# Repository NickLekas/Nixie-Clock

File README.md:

v1 is broken and required some bodge wires to work. I have not updated the schematic and PCB to correct my mistakes. It also has some deficencies in the dimming circuit resulint in a quiet, but audible whine.

v2 is in progress and will fix many issues and make the clock easier to update. It wil be using an RP2040.

Features
- Automatic time seting using GPS
- User sets their time zone using dip switches
- Tubes dim with ambient light
- Day light savings time will be controlled using a +/-1 switch 
- Plenty of test points for testing and hacking
- USB C for power and data

The goal of this is to be a program once project so the end user will never need to plug it into a computer. But if they do, the RP2040 will make firmware updates easy

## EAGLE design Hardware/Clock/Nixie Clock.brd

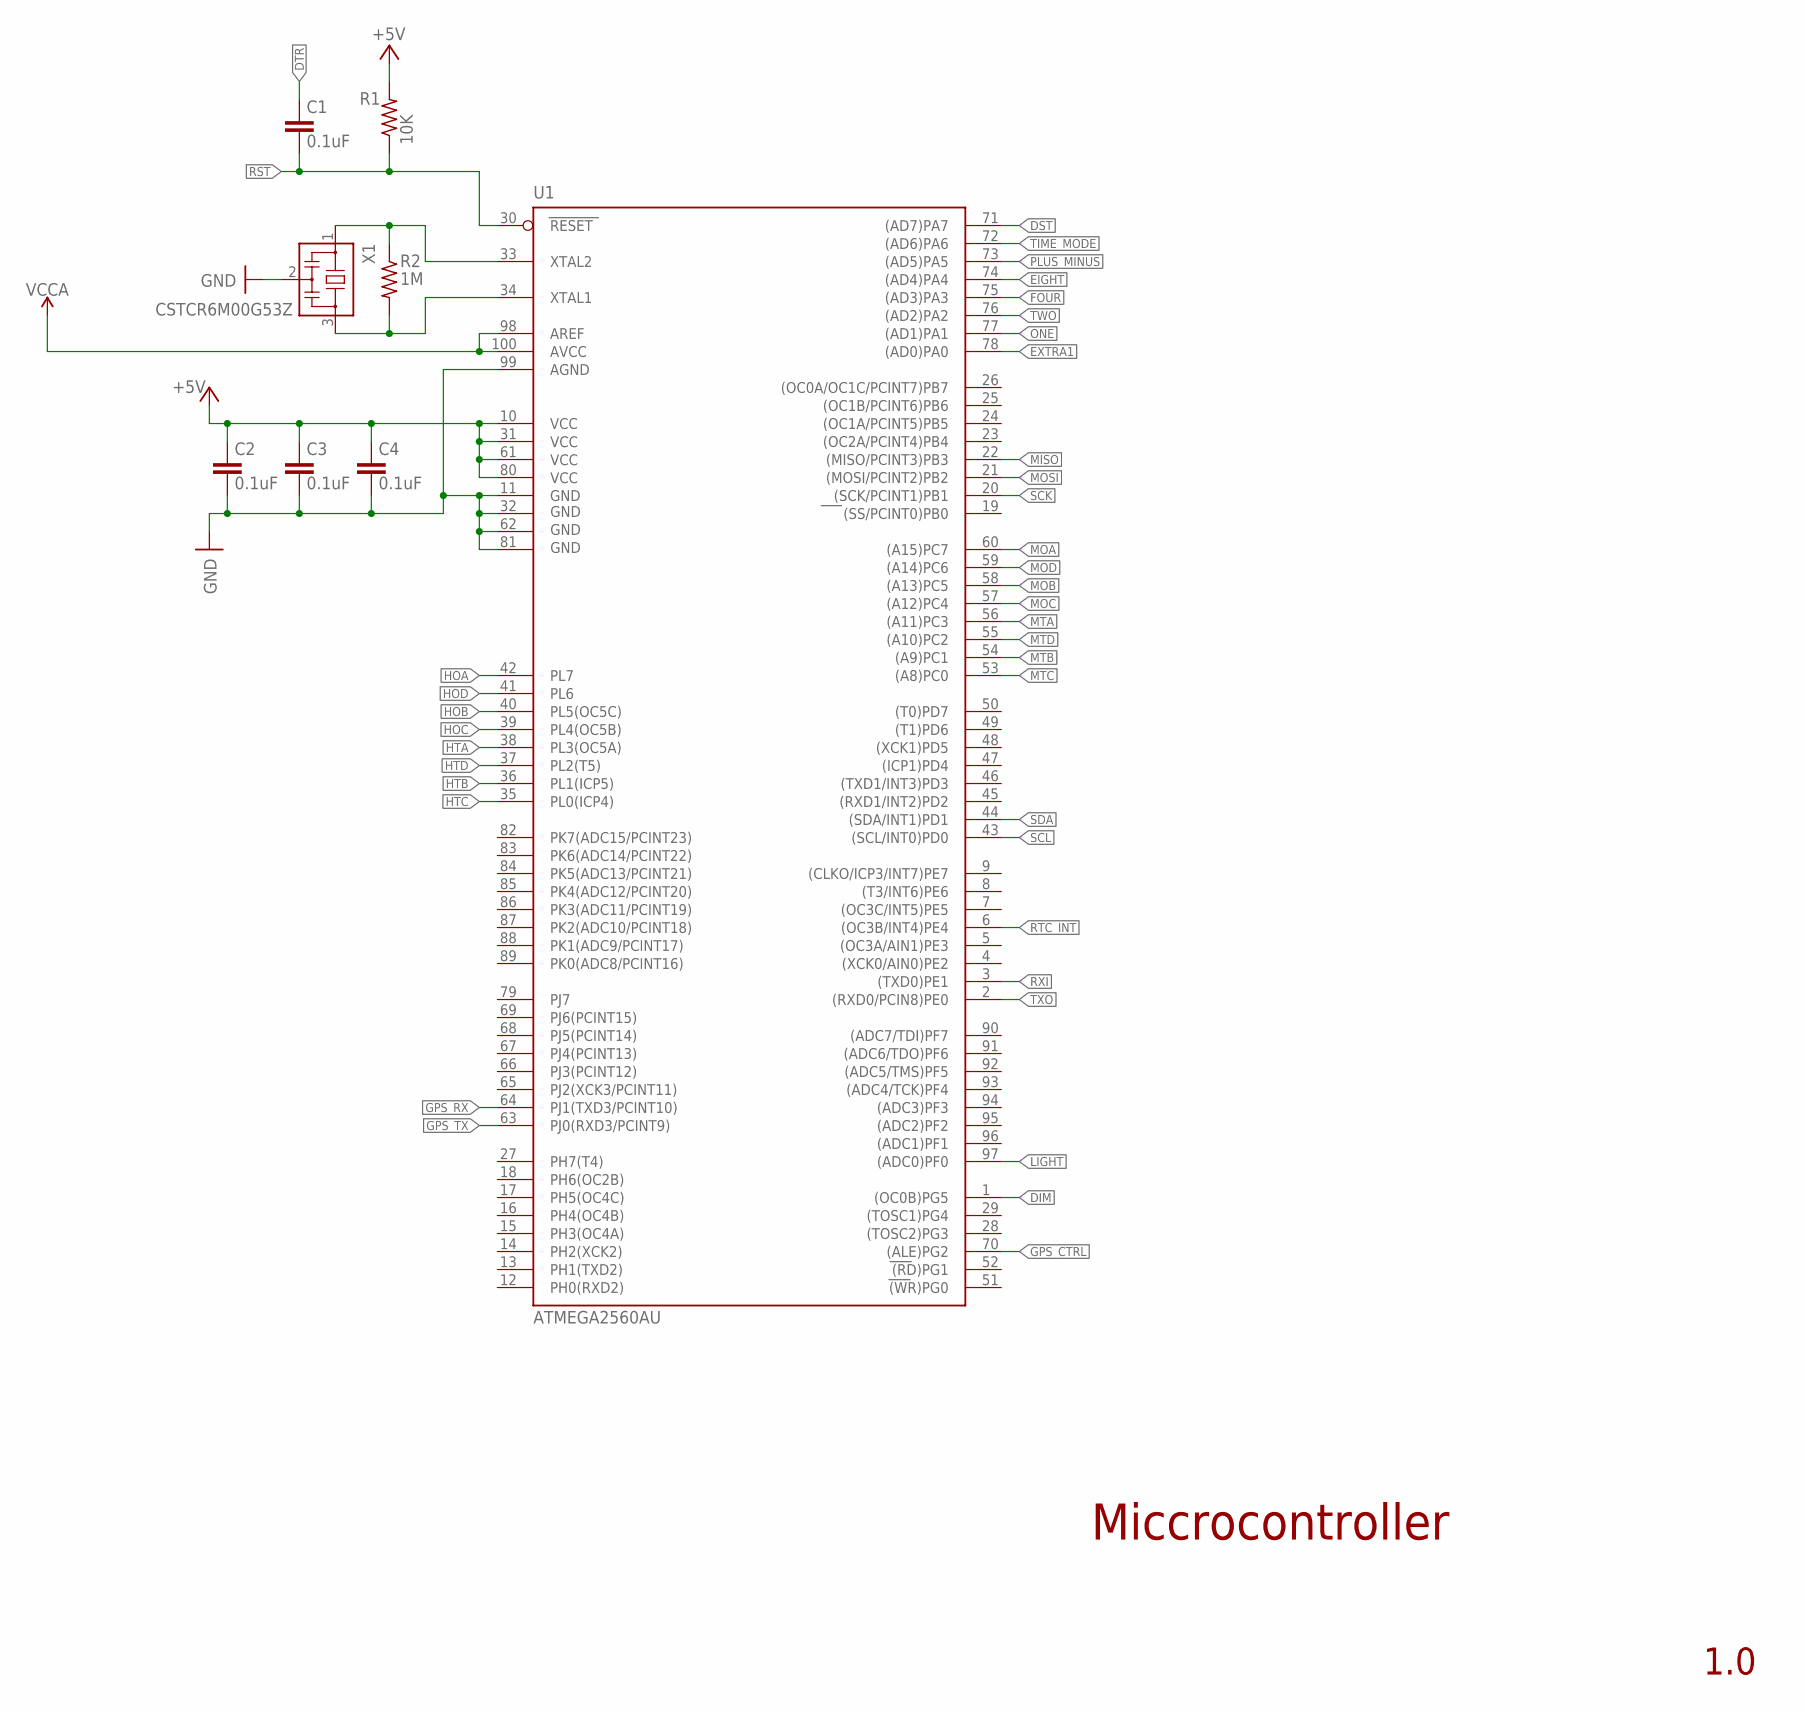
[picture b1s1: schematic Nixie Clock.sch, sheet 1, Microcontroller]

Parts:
C1, C2, C3, C4: 0.1uF; C0603
R1: 10K; R0603
R2: 1M; R0603
U1: ATMEGA2560AU; TQFP100; MPN ATMEGA2560-16AU
X1: CSTCR6M00G53Z; CSTCR6M; MPN CSTCE16M0V13C99-R0

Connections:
+5V: C2.1, C3.1, C4.1, R1.2, U1.10 (VCC), U1.31 (VCC1), U1.61 (VCC2), U1.80 (VCC3); also elsewhere on the board
DIM: U1.1 ((OC0B)PG5); also elsewhere on the board
DST: U1.71 ((AD7)PA7); also elsewhere on the board
DTR: C1.1; also elsewhere on the board
EIGHT: U1.74 ((AD4)PA4); also elsewhere on the board
EXTRA1: U1.78 ((AD0)PA0); also elsewhere on the board
FOUR: U1.75 ((AD3)PA3); also elsewhere on the board
GND: C2.2, C3.2, C4.2, U1.11 (GND), U1.32 (GND1), U1.62 (GND2), U1.81 (GND3), U1.99 (AGND), X1.2; also elsewhere on the board
GPS_CTRL: U1.70 ((ALE)PG2); also elsewhere on the board
GPS_RX: U1.64 (PJ1(TXD3/PCINT10)); also elsewhere on the board
GPS_TX: U1.63 (PJ0(RXD3/PCINT9)); also elsewhere on the board
HOA: U1.42 (PL7); also elsewhere on the board
HOB: U1.40 (PL5(OC5C)); also elsewhere on the board
HOC: U1.39 (PL4(OC5B)); also elsewhere on the board
HOD: U1.41 (PL6); also elsewhere on the board
HTA: U1.38 (PL3(OC5A)); also elsewhere on the board
HTB: U1.36 (PL1(ICP5)); also elsewhere on the board
HTC: U1.35 (PL0(ICP4)); also elsewhere on the board
HTD: U1.37 (PL2(T5)); also elsewhere on the board
LIGHT: U1.97 ((ADC0)PF0); also elsewhere on the board
MISO: U1.22 ((MISO/PCINT3)PB3); also elsewhere on the board
MOA: U1.60 ((A15)PC7); also elsewhere on the board
MOB: U1.58 ((A13)PC5); also elsewhere on the board
MOC: U1.57 ((A12)PC4); also elsewhere on the board
MOD: U1.59 ((A14)PC6); also elsewhere on the board
MOSI: U1.21 ((MOSI/PCINT2)PB2); also elsewhere on the board
MTA: U1.56 ((A11)PC3); also elsewhere on the board
MTB: U1.54 ((A9)PC1); also elsewhere on the board
MTC: U1.53 ((A8)PC0); also elsewhere on the board
MTD: U1.55 ((A10)PC2); also elsewhere on the board
unnamed: R2.2, U1.34 (XTAL1), X1.3
unnamed: R2.1, U1.33 (XTAL2), X1.1
ONE: U1.77 ((AD1)PA1); also elsewhere on the board
PLUS_MINUS: U1.73 ((AD5)PA5); also elsewhere on the board
RST: C1.2, R1.1, U1.30 (RESET); also elsewhere on the board
RTC_INT: U1.6 ((OC3B/INT4)PE4); also elsewhere on the board
RXI: U1.3 ((TXD0)PE1); also elsewhere on the board
SCK: U1.20 ((SCK/PCINT1)PB1); also elsewhere on the board
SCL: U1.43 ((SCL/INT0)PD0); also elsewhere on the board
SDA: U1.44 ((SDA/INT1)PD1); also elsewhere on the board
TIME_MODE: U1.72 ((AD6)PA6); also elsewhere on the board
TWO: U1.76 ((AD2)PA2); also elsewhere on the board
TXO: U1.2 ((RXD0/PCIN8)PE0); also elsewhere on the board
VCCA: U1.98 (AREF), U1.100 (AVCC); also elsewhere on the board

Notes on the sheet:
Miccrocontroller
1.0

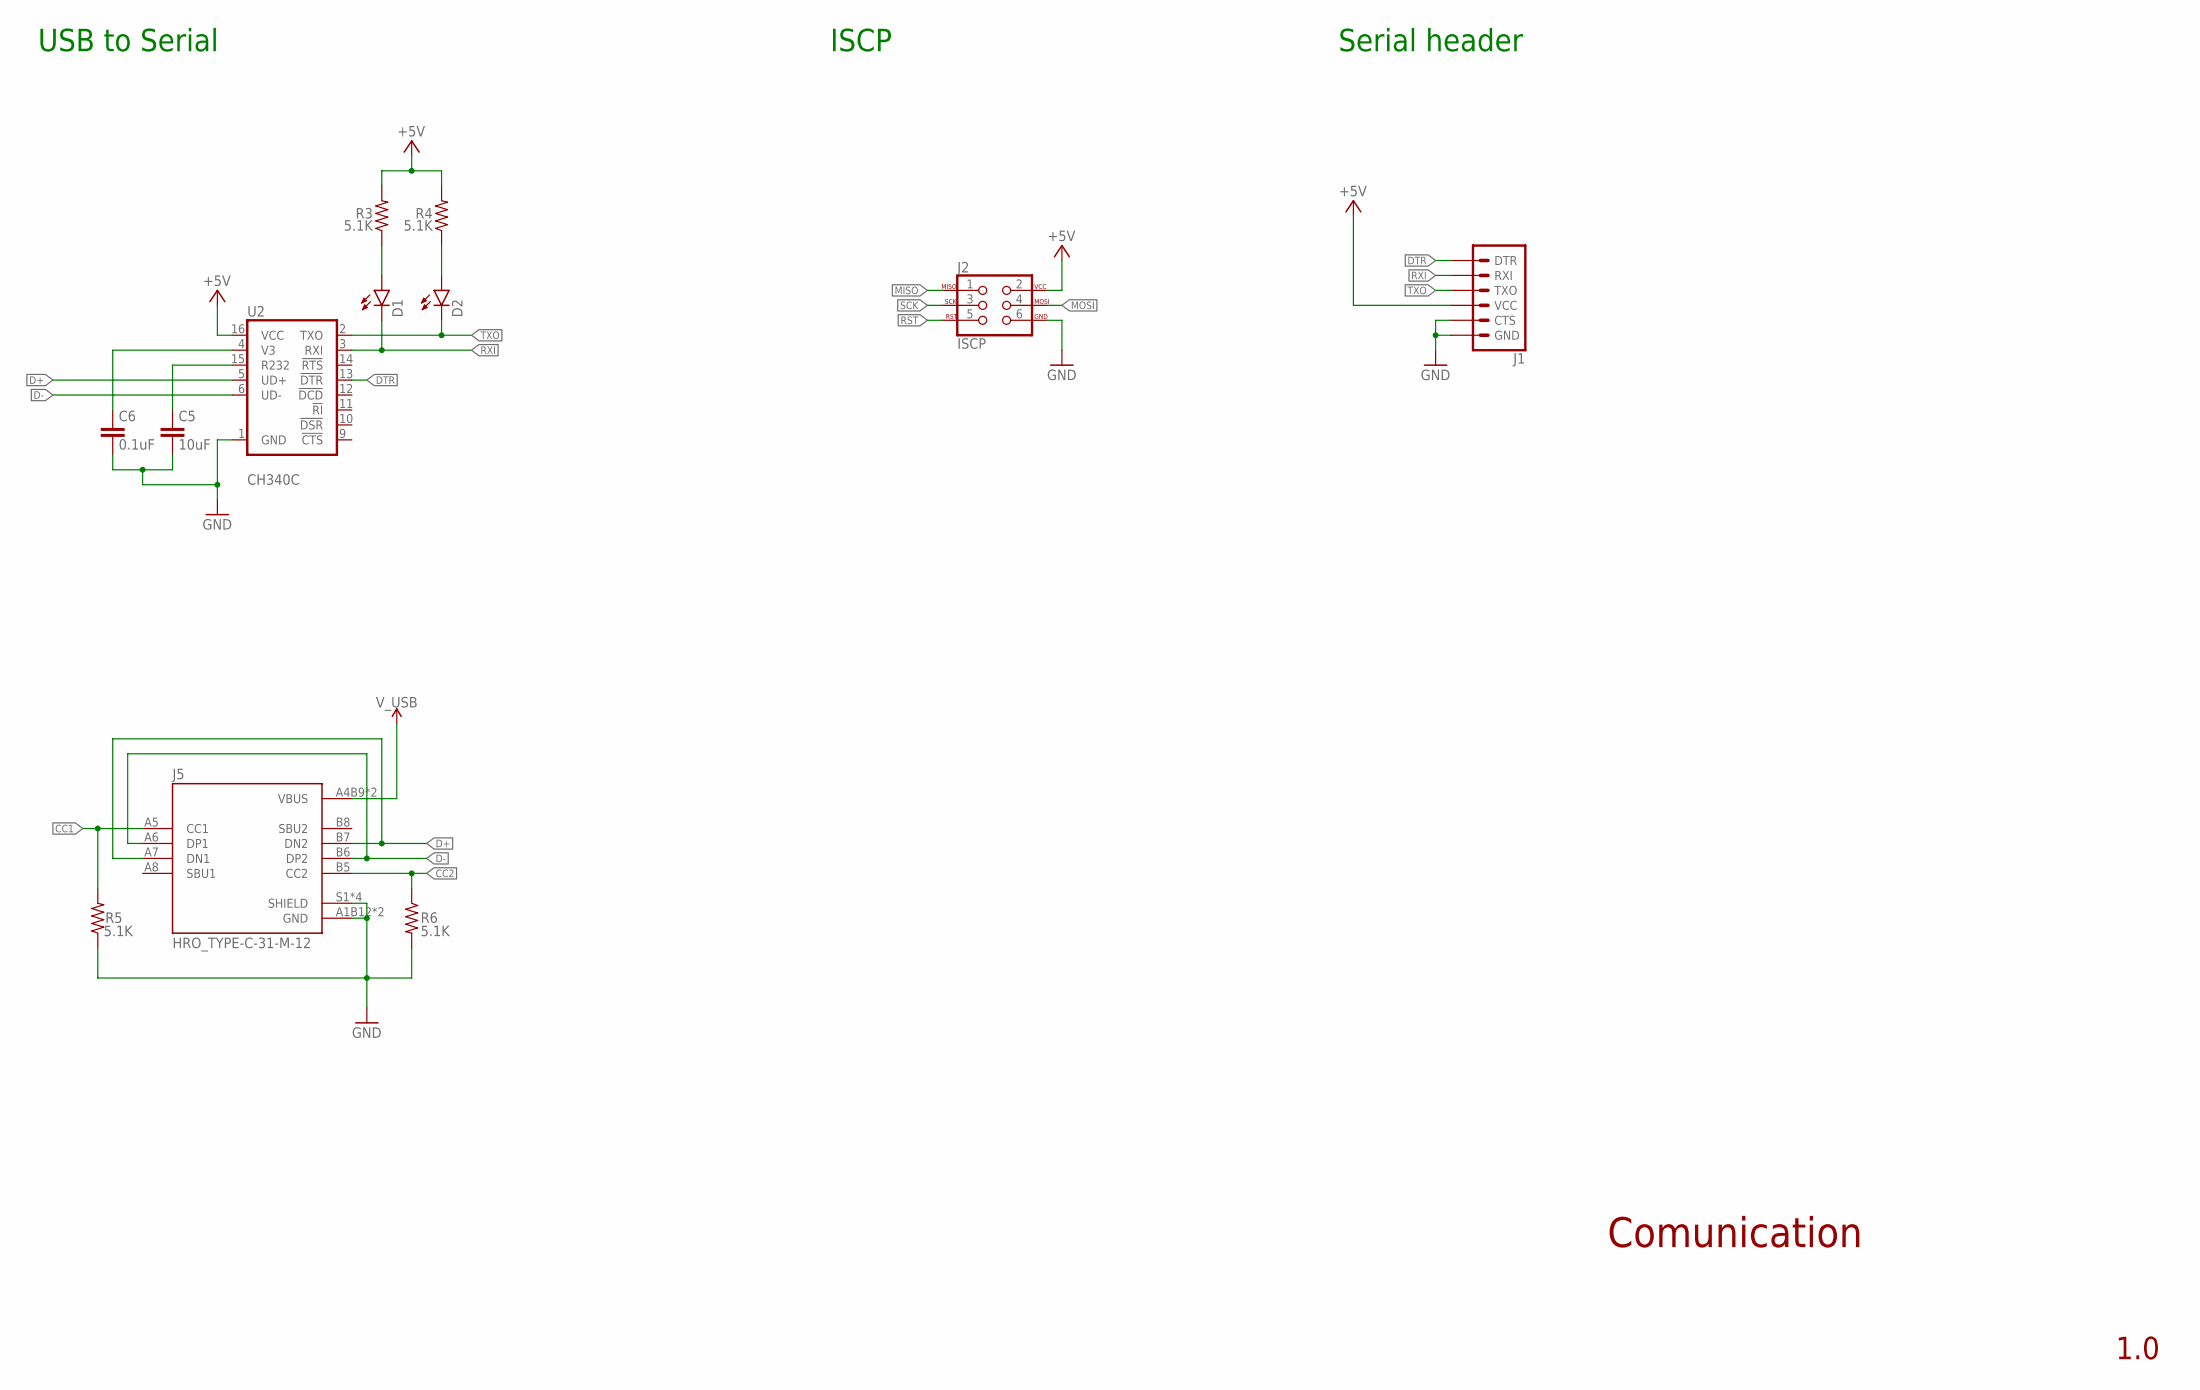
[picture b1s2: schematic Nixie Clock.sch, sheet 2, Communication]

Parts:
C5: 10uF; C0603
C6: 0.1uF; C0603
D1, D2: LEDCHIP-LED0603; CHIP-LED0603
J1: 6_PIN_SERIAL_TARGETSILK; 6_PIN_SERIAL_TARGET_SIDE_W_SILK
J2: ISCP; 2X3
J5: HRO_TYPE-C-31-M-12
R3, R4, R5, R6: 5.1K; R0603
U2: CH340C; SO016; MPN CH340C

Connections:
+5V: J1.P$4 (VCC), J2.2, R3.2, R4.2, U2.16 (VCC); also elsewhere on the board
CC1: J5.A5 (CC1), R5.2; also elsewhere on the board
CC2: J5.B5 (CC2), R6.1; also elsewhere on the board
D+: J5.A7 (DN1), J5.B7 (DN2), U2.5 (UD+)
D-: J5.A6 (DP1), J5.B6 (DP2), U2.6 (UD-)
DTR: J1.P$1 (DTR), U2.13 (!DTR); also elsewhere on the board
GND: C5.2, C6.2, J1.P$5 (CTS), J1.P$6 (GND), J2.6, J5.A1B12 (GND), J5.B1A12 (GND), J5.S1 (SHIELD), J5.S2 (SHIELD), J5.S3 (SHIELD), J5.S4 (SHIELD), R5.1, R6.2, U2.1 (GND); also elsewhere on the board
MISO: J2.1; also elsewhere on the board
MOSI: J2.4; also elsewhere on the board
unnamed: C5.1, U2.15 (R232)
unnamed: C6.1, U2.4 (V3)
unnamed: D1.A, R3.1
unnamed: D2.A, R4.1
RST: J2.5; also elsewhere on the board
RXI: D1.C, J1.P$3 (RXI), U2.3 (RXI); also elsewhere on the board
SCK: J2.3; also elsewhere on the board
TXO: D2.C, J1.P$2 (TXO), U2.2 (TXO); also elsewhere on the board
V_USB: J5.A4B9 (VBUS), J5.B4A9 (VBUS); also elsewhere on the board

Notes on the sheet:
USB to Serial
Comunication
1.0
ISCP
Serial header

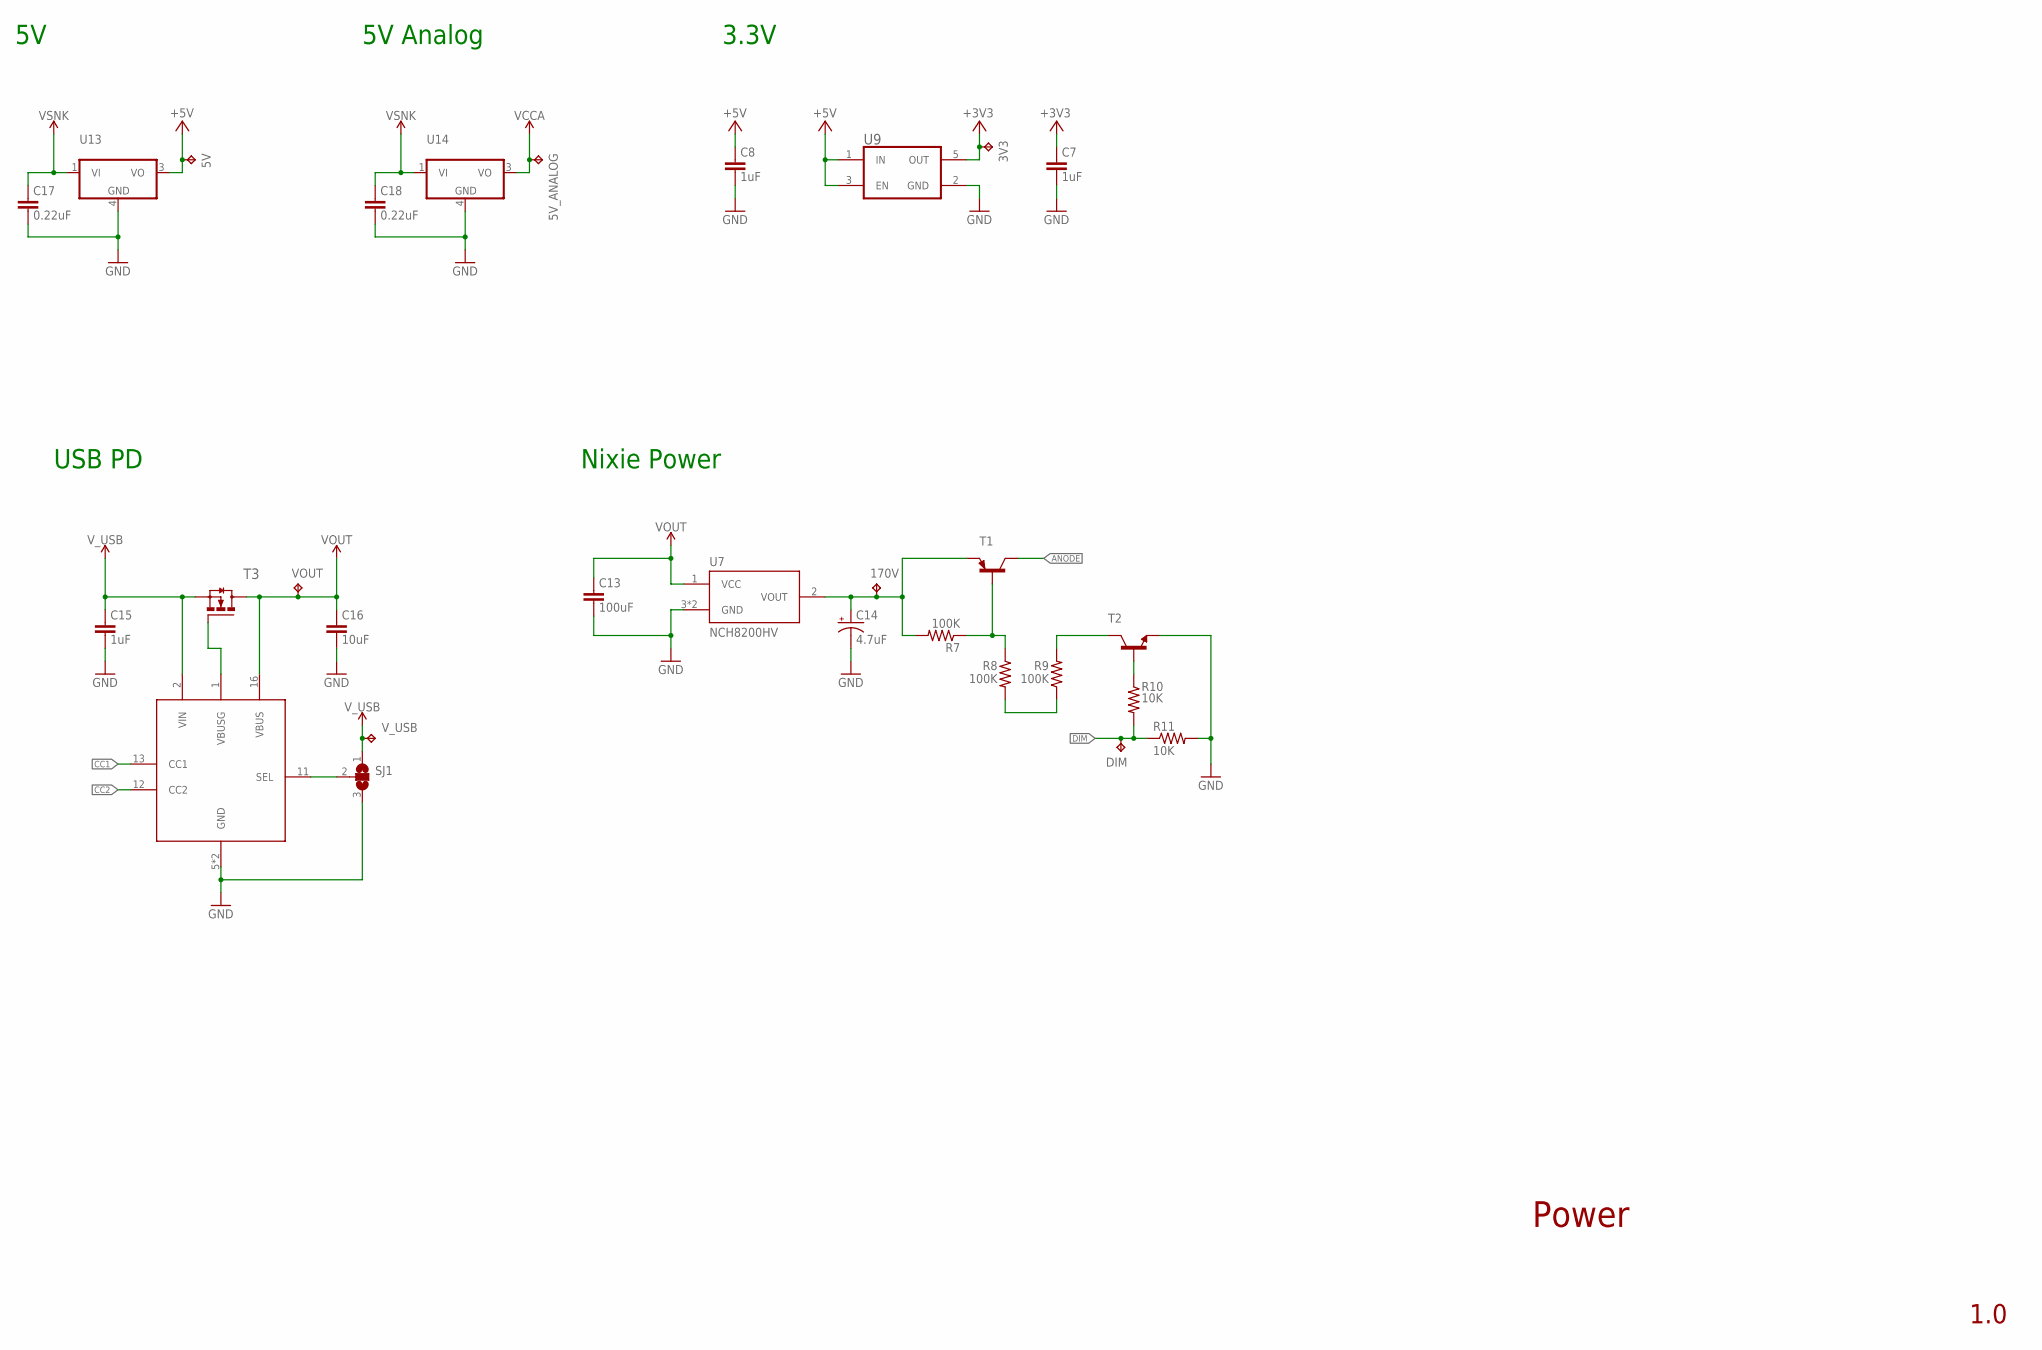
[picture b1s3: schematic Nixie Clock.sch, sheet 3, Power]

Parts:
3V3, 5V, 5V_ANALOG, 170V: TPPAD1-13; P1-13
C7, C8, C15: 1uF; C0603
C13: 100uF; C0603
C14: 4.7uF; E3,5-8
C16: 10uF; C0603
C17, C18: 0.22uF; C0603
DIM: TPPAD1-13; P1-13
R7, R8, R9: 100K; R0603
R10, R11: 10K; R0603
SJ1: SJ2W; SJ_2
T1: PZTA92; SOT223
T2: PZTA42; SOT223
T3: CSD18543Q3A; VSONP-8
U7: NCH8200HV
U9: MIC5504-3.3YM5TR; SOT95P280X130-5N; MPN MIC5504-3.3YM5-TR
U12: IP2721; TSSOP16EXP
U13: LM340MP-05; SOT223; MPN LM340MP-5.0/NOPB
U14: LM340MP-05; SOT223
VOUT: TPPAD1-13; P1-13
V_USB: TPPAD1-13; P1-13

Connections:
+3V3: 3V3.TP, C7.1, U9.5 (OUT); also elsewhere on the board
+5V: 5V.TP, C8.1, U9.1 (IN), U9.3 (EN), U13.3 (VO); also elsewhere on the board
ANODE: T1.2 (C), T1.4 (C); also elsewhere on the board
CC1: U12.13 (CC1); also elsewhere on the board
CC2: U12.12 (CC2); also elsewhere on the board
DIM: DIM.TP, R10.2, R11.1; also elsewhere on the board
GND: C7.2, C8.2, C13.2, C14.-, C15.2, C16.2, C17.2, C18.2, R11.2, SJ1.3, T2.3 (E), U7.3 (GND), U7.4 (GND), U9.2 (GND), U12.5 (GND), U12.EXP (GND), U13.4 (GND), U14.4 (GND); also elsewhere on the board
unnamed: T3.4 (G), U12.1 (VBUSG)
unnamed: SJ1.2, U12.11 (SEL)
unnamed: R10.1, T2.1 (B)
unnamed: 170V.TP, C14.+, R7.2, T1.3 (E), U7.2 (VOUT)
unnamed: R7.1, R8.1, T1.1 (B)
unnamed: R9.2, T2.2 (C), T2.4 (C)
unnamed: R8.2, R9.1
VCCA: 5V_ANALOG.TP, U14.3 (VO); also elsewhere on the board
VOUT: C13.1, C16.1, C17.1, C18.1, T3.5 (D), T3.6 (D), T3.7 (D), T3.8 (D), T3.9 (D), T3.10 (D), T3.11 (D), T3.12 (D), U7.1 (VCC), U12.16 (VBUS), U13.1 (VI), U14.1 (VI), VOUT.TP
V_USB: C15.1, SJ1.1, T3.1 (S), T3.2 (S), T3.3 (S), U12.2 (VIN), V_USB.TP; also elsewhere on the board

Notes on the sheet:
Nixie Power
3.3V
Power
1.0
USB PD
5V Analog

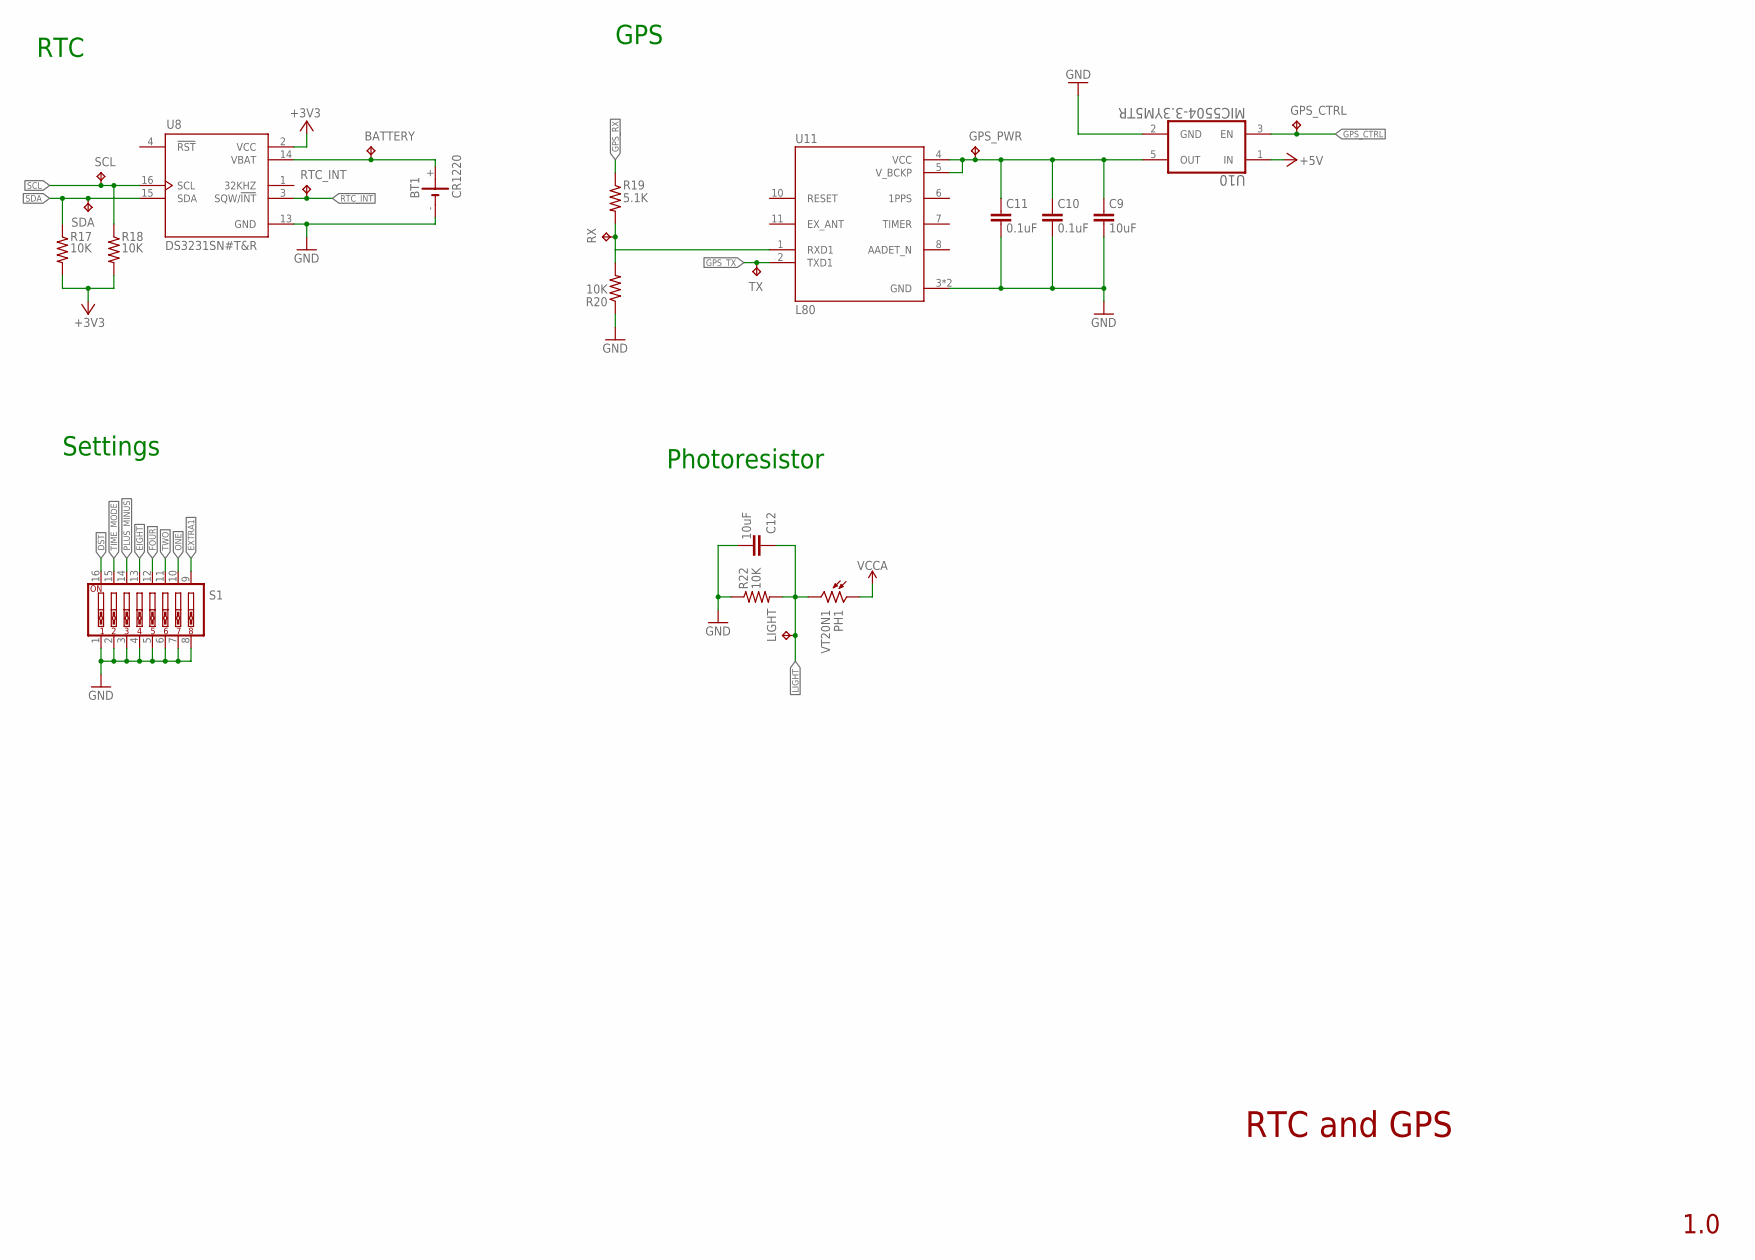
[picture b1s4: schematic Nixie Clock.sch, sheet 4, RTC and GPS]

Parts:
BATTERY: TPPAD1-13; P1-13
BT1: CR1220; CH291-1220LF
C9, C12: 10uF; C0603
C10, C11: 0.1uF; C0603
GPS_CTRL: TPPAD1-13; P1-13
GPS_PWR: TPPAD1-13; P1-13
LIGHT: TPPAD1-13; P1-13
PH1: VT20N1; TO46-VT200
R17, R18, R20, R22: 10K; R0603
R19: 5.1K; R0603
RTC_INT: TPPAD1-13; P1-13
RX: TPPAD1-13; P1-13
S1: SW_DIP-8; EDG-08
SCL: TPPAD1-13; P1-13
SDA: TPPAD1-13; P1-13
TX: TPPAD1-13; P1-13
U8: DS3231SN#T&R; SOIC127P1032X265-16N
U10: MIC5504-3.3YM5TR; SOT95P280X130-5N; MPN MIC5504-3.3YM5-TR
U11: L80; XCVR_L80

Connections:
+3V3: R17.2, R18.2, U8.2 (VCC); also elsewhere on the board
+5V: U10.1 (IN); also elsewhere on the board
DST: S1.16; also elsewhere on the board
EIGHT: S1.13; also elsewhere on the board
EXTRA1: S1.9; also elsewhere on the board
FOUR: S1.12; also elsewhere on the board
GND: BT1.-, C9.2, C10.2, C11.2, C12.2, R20.1, R22.1, S1.1, S1.2, S1.3, S1.4, S1.5, S1.6, S1.7, S1.8, U8.13 (GND), U10.2 (GND), U11.3 (GND), U11.12 (GND); also elsewhere on the board
GPS_CTRL: GPS_CTRL.TP, U10.3 (EN); also elsewhere on the board
GPS_RX: R19.1; also elsewhere on the board
GPS_TX: TX.TP, U11.2 (TXD1); also elsewhere on the board
LIGHT: C12.1, LIGHT.TP, PH1.2, R22.2; also elsewhere on the board
unnamed: BATTERY.TP, BT1.+, U8.14 (VBAT)
unnamed: C9.1, C10.1, C11.1, GPS_PWR.TP, U10.5 (OUT), U11.4 (VCC), U11.5 (V_BCKP)
unnamed: R19.2, R20.2, RX.TP, U11.1 (RXD1)
ONE: S1.10; also elsewhere on the board
PLUS_MINUS: S1.14; also elsewhere on the board
RTC_INT: RTC_INT.TP, U8.3 (SQW/!INT); also elsewhere on the board
SCL: R18.1, SCL.TP, U8.16 (SCL); also elsewhere on the board
SDA: R17.1, SDA.TP, U8.15 (SDA); also elsewhere on the board
TIME_MODE: S1.15; also elsewhere on the board
TWO: S1.11; also elsewhere on the board
VCCA: PH1.1; also elsewhere on the board

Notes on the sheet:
RTC
GPS
RTC and GPS
1.0
Settings
Photoresistor

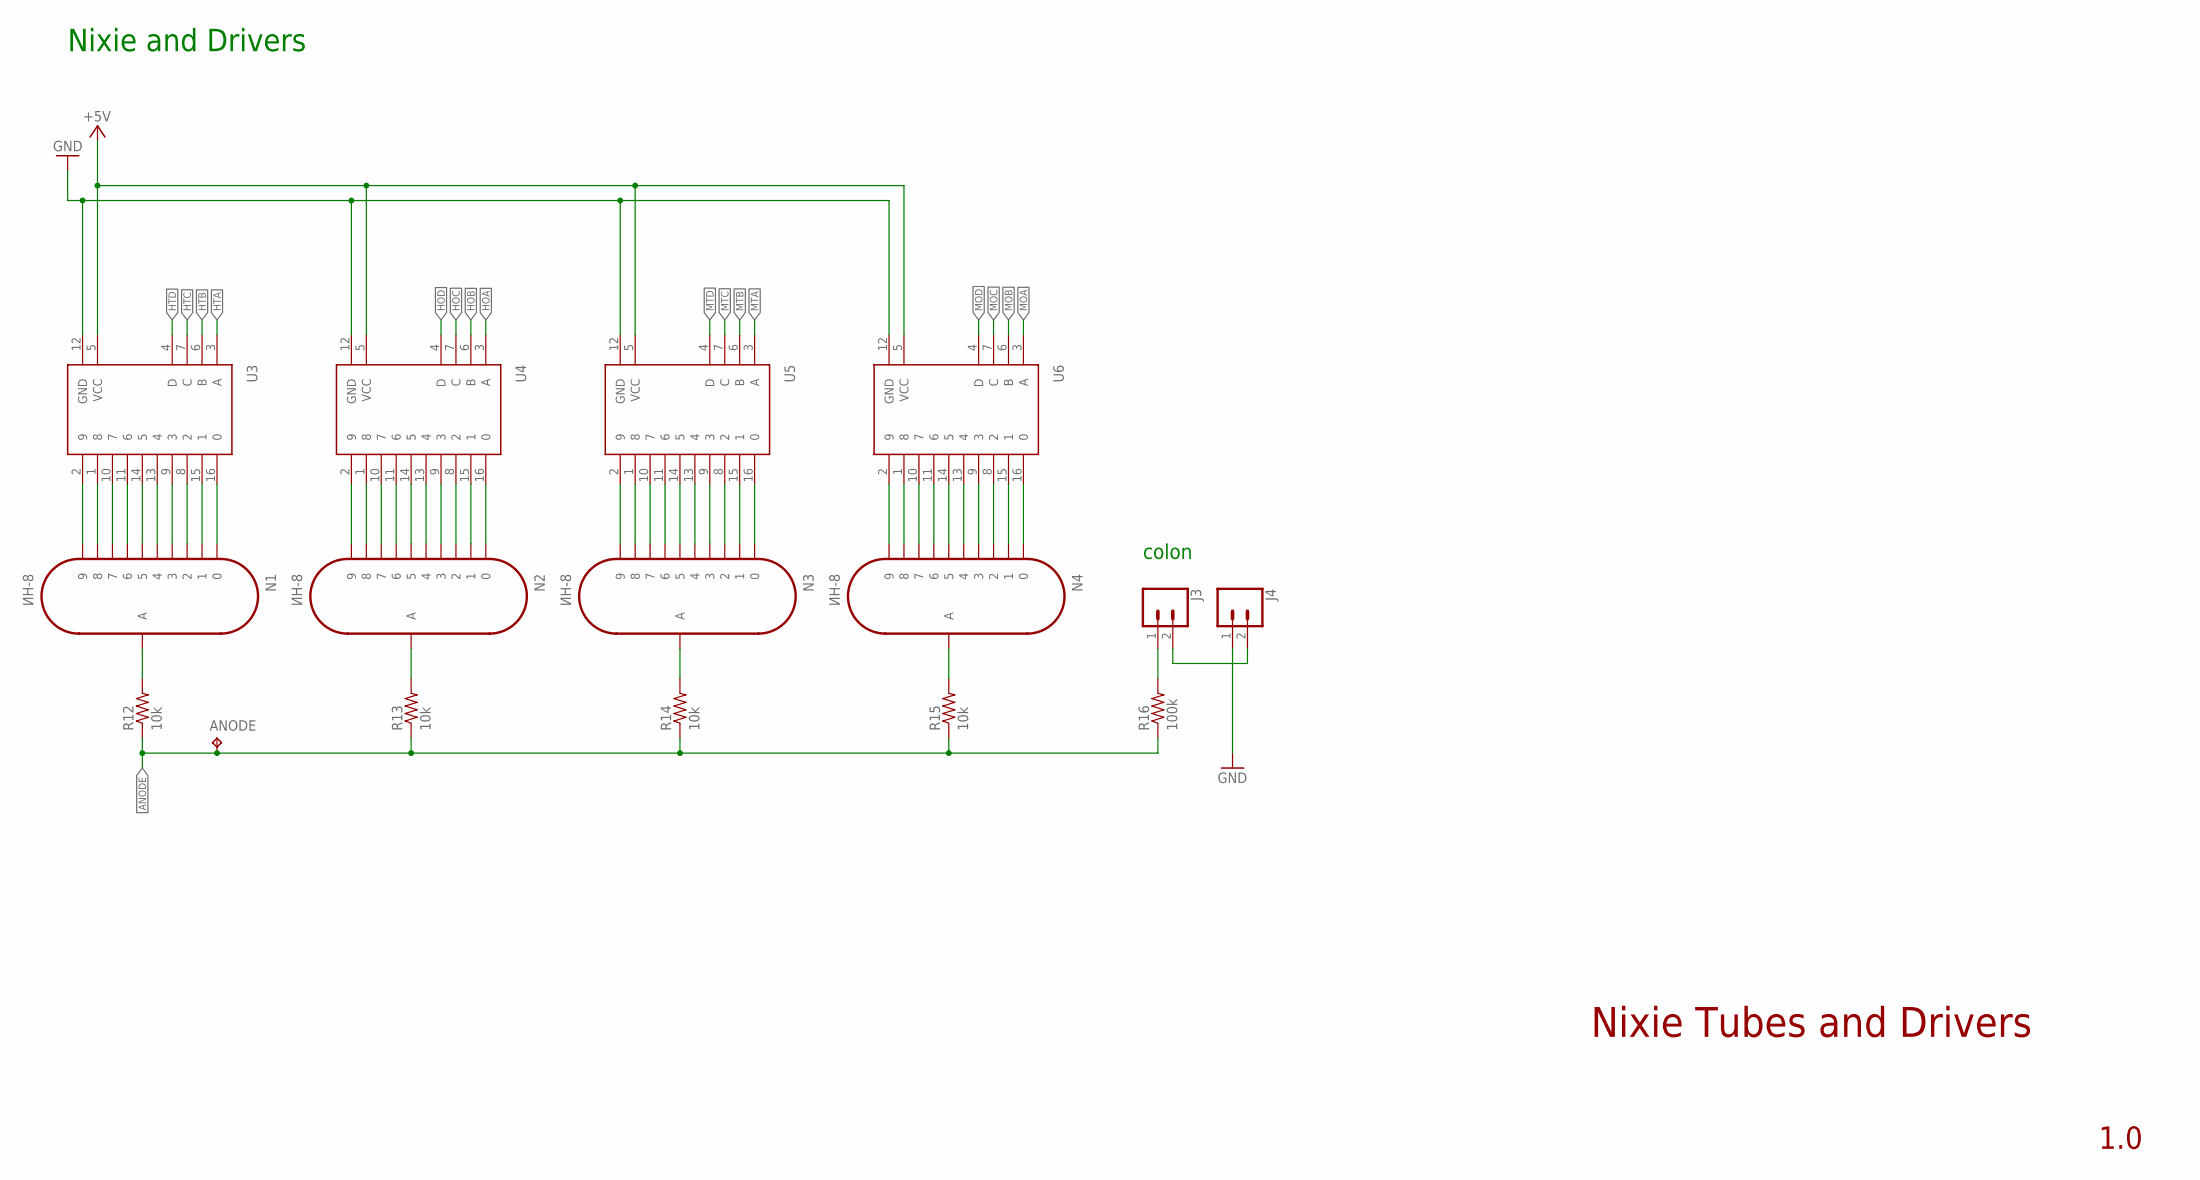
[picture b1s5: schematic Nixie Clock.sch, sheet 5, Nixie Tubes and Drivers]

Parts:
ANODE: TPPAD1-13; P1-13
J3, J4: CONN_02LOCK_LONGPADS; 1X02_LOCK_LONGPADS
N1, N2, N3, N4: ИН-8; IN-8_SOCKET
R12, R13, R14, R15: 10k; M0805
R16: 100k; R0603
U3, U4, U5, U6: K155ID1; DIL16-KIT

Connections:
+5V: U3.5 (VCC), U4.5 (VCC), U5.5 (VCC), U6.5 (VCC); also elsewhere on the board
ANODE: ANODE.TP, R12.1, R13.1, R14.1, R15.1, R16.1; also elsewhere on the board
GND: J4.1, U3.12 (GND), U4.12 (GND), U5.12 (GND), U6.12 (GND); also elsewhere on the board
HOA: U4.3 (A); also elsewhere on the board
HOB: U4.6 (B); also elsewhere on the board
HOC: U4.7 (C); also elsewhere on the board
HOD: U4.4 (D); also elsewhere on the board
HTA: U3.3 (A); also elsewhere on the board
HTB: U3.6 (B); also elsewhere on the board
HTC: U3.7 (C); also elsewhere on the board
HTD: U3.4 (D); also elsewhere on the board
MOA: U6.3 (A); also elsewhere on the board
MOB: U6.6 (B); also elsewhere on the board
MOC: U6.7 (C); also elsewhere on the board
MOD: U6.4 (D); also elsewhere on the board
MTA: U5.3 (A); also elsewhere on the board
MTB: U5.6 (B); also elsewhere on the board
MTC: U5.7 (C); also elsewhere on the board
MTD: U5.4 (D); also elsewhere on the board
unnamed: J3.1, R16.2
unnamed: J3.2, J4.2
unnamed: N1.9, U3.2 (9)
unnamed: N1.8, U3.1 (8)
unnamed: N1.7, U3.10 (7)
unnamed: N1.6, U3.11 (6)
unnamed: N1.5, U3.14 (5)
unnamed: N1.4, U3.13 (4)
unnamed: N1.3, U3.9 (3)
unnamed: N1.2, U3.8 (2)
unnamed: N1.1, U3.15 (1)
unnamed: N1.0, U3.16 (0)
unnamed: N1.A, R12.2
unnamed: N2.9, U4.2 (9)
unnamed: N2.8, U4.1 (8)
unnamed: N2.7, U4.10 (7)
unnamed: N2.6, U4.11 (6)
unnamed: N2.5, U4.14 (5)
unnamed: N2.4, U4.13 (4)
unnamed: N2.3, U4.9 (3)
unnamed: N2.2, U4.8 (2)
unnamed: N2.1, U4.15 (1)
unnamed: N2.0, U4.16 (0)
unnamed: N2.A, R13.2
unnamed: N3.9, U5.2 (9)
unnamed: N3.8, U5.1 (8)
unnamed: N3.7, U5.10 (7)
unnamed: N3.6, U5.11 (6)
unnamed: N3.5, U5.14 (5)
unnamed: N3.4, U5.13 (4)
unnamed: N3.3, U5.9 (3)
unnamed: N3.2, U5.8 (2)
unnamed: N3.1, U5.15 (1)
unnamed: N3.0, U5.16 (0)
unnamed: N3.A, R14.2
unnamed: N4.9, U6.2 (9)
unnamed: N4.8, U6.1 (8)
unnamed: N4.7, U6.10 (7)
unnamed: N4.6, U6.11 (6)
unnamed: N4.5, U6.14 (5)
unnamed: N4.4, U6.13 (4)
unnamed: N4.3, U6.9 (3)
unnamed: N4.2, U6.8 (2)
unnamed: N4.1, U6.15 (1)
unnamed: N4.0, U6.16 (0)
unnamed: N4.A, R15.2

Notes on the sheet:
Nixie and Drivers
Nixie Tubes and Drivers
1.0
colon

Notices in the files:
parts and their libraries:
SparkFun-Connectors: Licensing: Creative Commons ShareAlike 4.0 International - https://creativecommons.org/licenses/by-sa/4.0
